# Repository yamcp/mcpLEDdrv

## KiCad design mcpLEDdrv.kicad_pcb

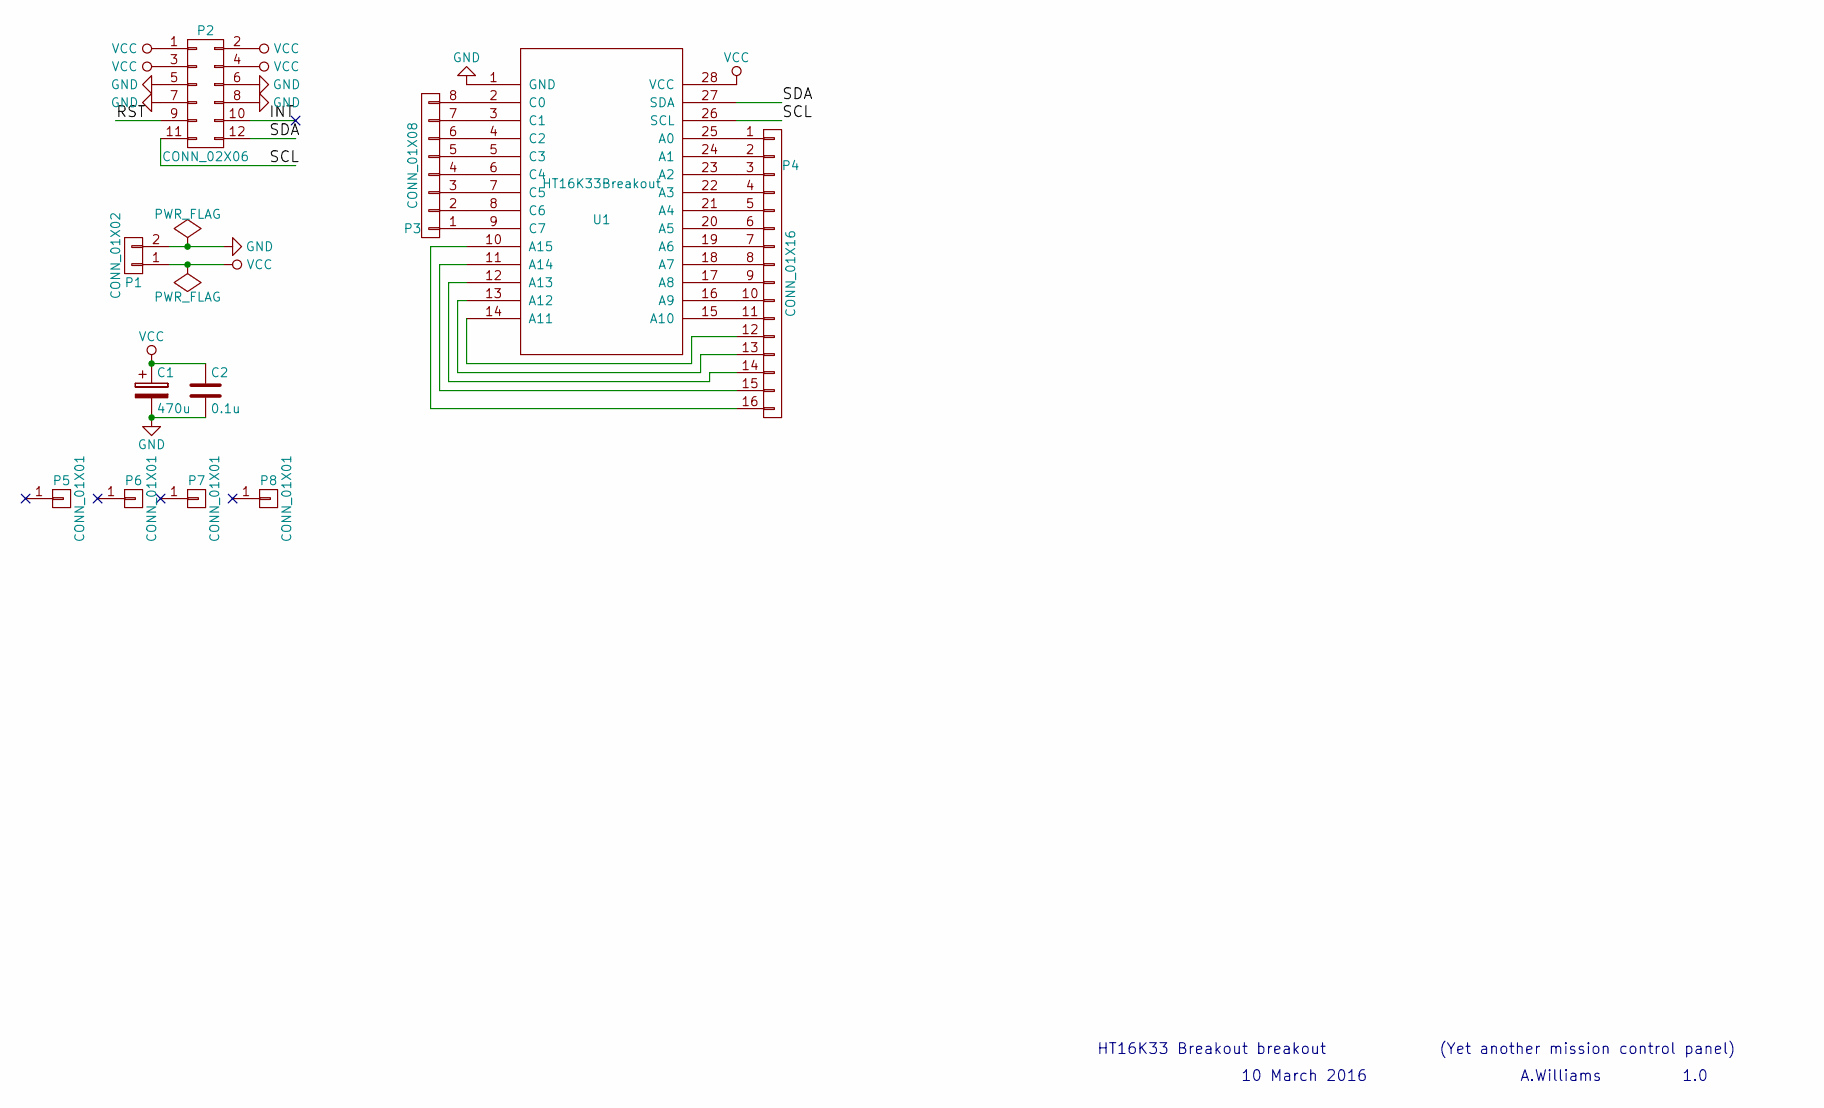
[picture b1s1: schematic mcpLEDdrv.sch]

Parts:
C1: 470u; C_Radial_D8_L13_P3.8
C2: 0.1u; C_Rect_L7_W2_P5
P1: CONN_01X02; bornier2
P2: CONN_02X06; IDC_Header_Straight_12pins
P3: CONN_01X08; Pin_Header_Straight_1x08
P4: CONN_01X16; Pin_Header_Straight_1x16
P5, P6, P7, P8: CONN_01X01; MountingHole_3.5mm_Pad
U1: HT16K33Breakout; DIP-28_W15.24mm

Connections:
/INT: P2.10
/RST: P2.9
/SCL: P2.11, U1.26 (SCL)
/SDA: P2.12, U1.27 (SDA)
GND: C1.2, C2.2, P1.2, P2.5, P2.6, P2.7, P2.8, U1.1 (GND)
unnamed: P3.1, U1.9 (C7)
unnamed: P3.2, U1.8 (C6)
unnamed: P3.3, U1.7 (C5)
unnamed: P3.4, U1.6 (C4)
unnamed: P3.5, U1.5 (C3)
unnamed: P3.6, U1.4 (C2)
unnamed: P3.7, U1.3 (C1)
unnamed: P3.8, U1.2 (C0)
unnamed: P4.1, U1.25 (A0)
unnamed: P4.2, U1.24 (A1)
unnamed: P4.3, U1.23 (A2)
unnamed: P4.4, U1.22 (A3)
unnamed: P4.5, U1.21 (A4)
unnamed: P4.6, U1.20 (A5)
unnamed: P4.7, U1.19 (A6)
unnamed: P4.8, U1.18 (A7)
unnamed: P4.9, U1.17 (A8)
unnamed: P4.10, U1.16 (A9)
unnamed: P4.11, U1.15 (A10)
unnamed: P4.12, U1.14 (A11)
unnamed: P4.13, U1.13 (A12)
unnamed: P4.14, U1.12 (A13)
unnamed: P4.15, U1.11 (A14)
unnamed: P4.16, U1.10 (A15)
VCC: C1.1, C2.1, P1.1, P2.1, P2.2, P2.3, P2.4, U1.28 (VCC)

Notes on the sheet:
HT16K33 Breakout breakout
10 March 2016
(Yet another mission control panel)
1.0
A.Williams

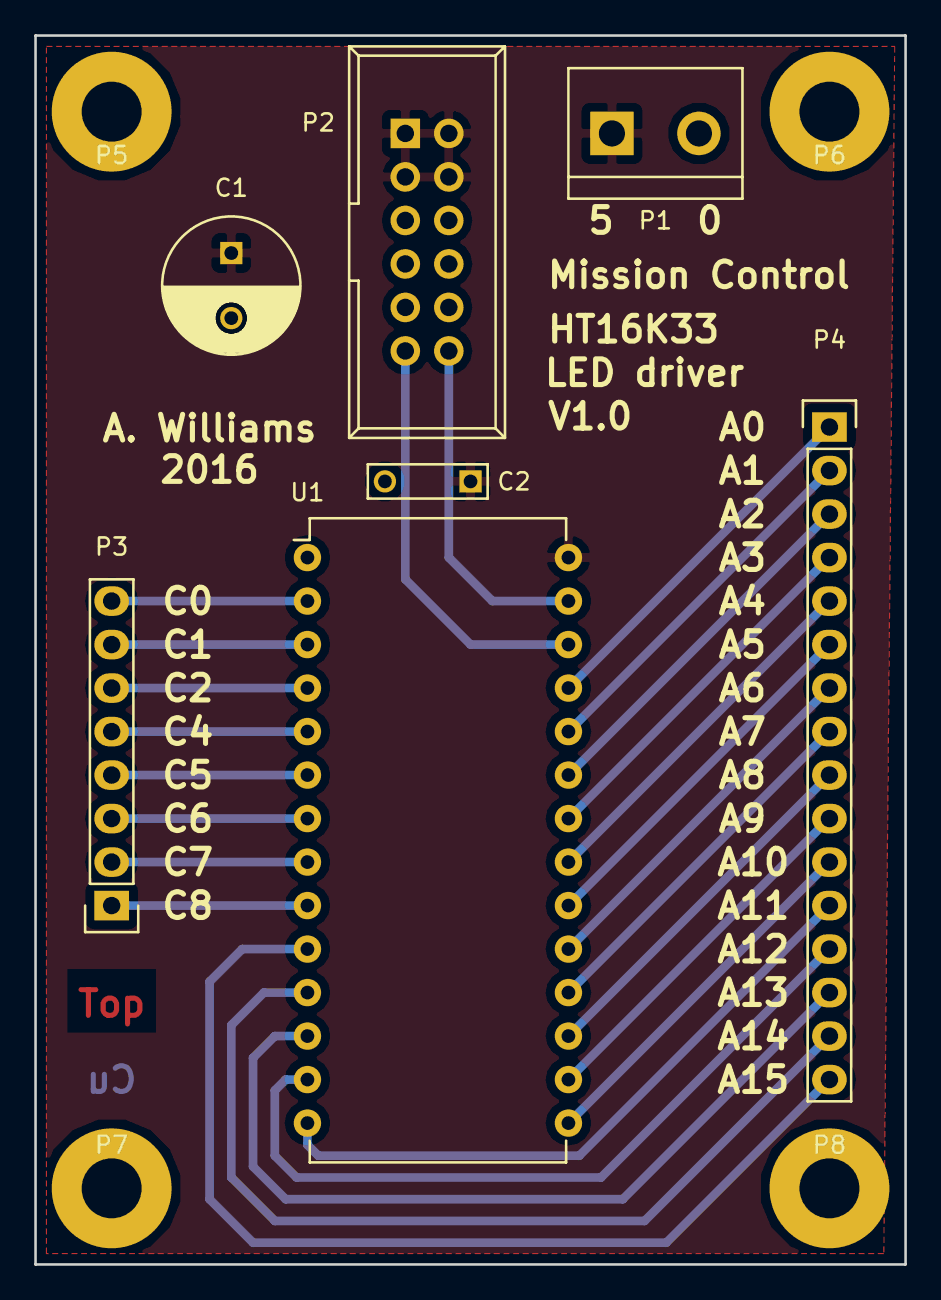
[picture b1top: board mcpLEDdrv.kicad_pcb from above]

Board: 2 copper layers, 50.8 x 71.8 mm, 11 parts (0 on the bottom side), 28 nets.
